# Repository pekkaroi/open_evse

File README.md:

# OpenEVSE

My fork has support for two contactors - one for 1 phase and one for 3 phase, and user can select the relay before starting charging. Change of the relay is forbidden during charging. To change the number of phases (to match with excess solar production), I have implemented a EspHome component connected to my OpenEvse directly with uart, and it first disables the charger (sleep), changes the relay to use, and then re-enables charge.

Additionally, as I accidentially ordered AtMega 328pb chips instead of 328p for my build, I had to modify the source accordinly.

Firmware for OpenEVSE controller used in OpenEVSE Charging Stations sold in the USA, and OpenEnergyMonitor EmonEVSE units sold in (UK/EU).

- OpenEVSE: <https://store.openevse.com/collections/all-products>
- EmonEVSE: <https://shop.openenergymonitor.com/evse/>

Based on OpenEVSE: Open Source Hardware J1772 Electric Vehicle Supply Equipment

## USA

TODO: add notes about USA OpenEVSE

## UK/EU

- Disable `AUTOSVCLEVEL` (autodetection is designed for split-phase)
- Charging level default to `L2`
- Set `MAX_CURRENT_CAPACITY_L2 32` (limit for single-phase charging in UK/EU)
- Add '.EU' to version number
- Enable LCD Redraw every couple of min (required for EMC/CE)

### EmonEVSE

EmonEVSE (non-tethered type-2 EVSE unit)

- `PP_AUTO_AMPACITY` enabled to set max current based on non-tethered cable connected
- Three-phase option with `THREEPHASE` enabled to calculate three-phase energy ( Unneeded with ESP32_WiFi firmware >= 4.2

## API Documentation

- WIFI API: <http://github.com/openevse/ESP32_WiFi_V4.x/>
- RAPI API: <https://github.com/openenergymonitor/open_evse/blob/master/firmware/open_evse/rapi_proc.h>

## Resources

- [OpenEnergyMonitor OpenEVSE Setup Guide](https://guide.openenergymonitor.org/integrations/openevse)
- [OpenEnergyMonitor OpenEVSE Shop](https://shop.openenergymonitor.com/ev-charging/)

- [OpenEVSE Controller Datasheet](https://github.com/OpenEVSE/OpenEVSE_PLUS/blob/master/OpenEVSE_PLUS_v5/OpenEVSE_Plus_v5.pdf)
- [OpenEVSE Controller Hardware Repo](https://github.com/OpenEVSE/OpenEVSE_PLUS)
- [OpenEVSE Project Homepage](https://openevse.com)

***

Firmware compile & upload help: [firmware/open_evse/LoadingFirmware.md](firmware/open_evse/LoadingFirmware.md)

NOTES:

- Working versions of the required libraries are included with the firmware code. This avoids potential issues related to using the wrong versions of the libraries.
- Highly recommend using the tested pre-compiled firmware (see releases page)

## Flash pre-compiled using avrdude

`$ avrdude -p atmega328p -B6 -c usbasp -P usb -e -U flash:w:firmware.hex`

ISP programmer required e.g [USBASP](https://www.amazon.co.uk/Hobby-Components-USBASP-Programmer-Adapter/dp/B06XYV162N)

### Set AVR fuses

This only needs to be done once in the factory

`avrdude -c USBasp -p m328p -U lfuse:w:0xFF:m -U hfuse:w:0xDF:m -U efuse:w:0xFD:m -B6`

If writing eFuse fails ISBasp may need a [firmware update](https://www.vishnumaiea.in/articles/electronics/how-to-solve-usbasp-avr-efuse-write-problem-on-progisp)

***

Tip Jar: I developed/maintain this firmware on a volunteer basis. Any donation, no matter how small, is greatly appreciated.

```text
Open EVSE is free software; you can redistribute it and/or modify
it under the terms of the GNU General Public License as published by
the Free Software Foundation; either version 3, or (at your option)
any later version.

Open EVSE is distributed in the hope that it will be useful,
but WITHOUT ANY WARRANTY; without even the implied warranty of
MERCHANTABILITY or FITNESS FOR A PARTICULAR PURPOSE.  See the
GNU General Public License for more details.

You should have received a copy of the GNU General Public License
along with Open EVSE; see the file COPYING.  If not, write to the
Free Software Foundation, Inc., 59 Temple Place - Suite 330,
Boston, MA 02111-1307, USA.

* Open EVSE is distributed in the hope that it will be useful,
* but WITHOUT ANY WARRANTY; without even the implied warranty of
* MERCHANTABILITY or FITNESS FOR A PARTICULAR PURPOSE.
```

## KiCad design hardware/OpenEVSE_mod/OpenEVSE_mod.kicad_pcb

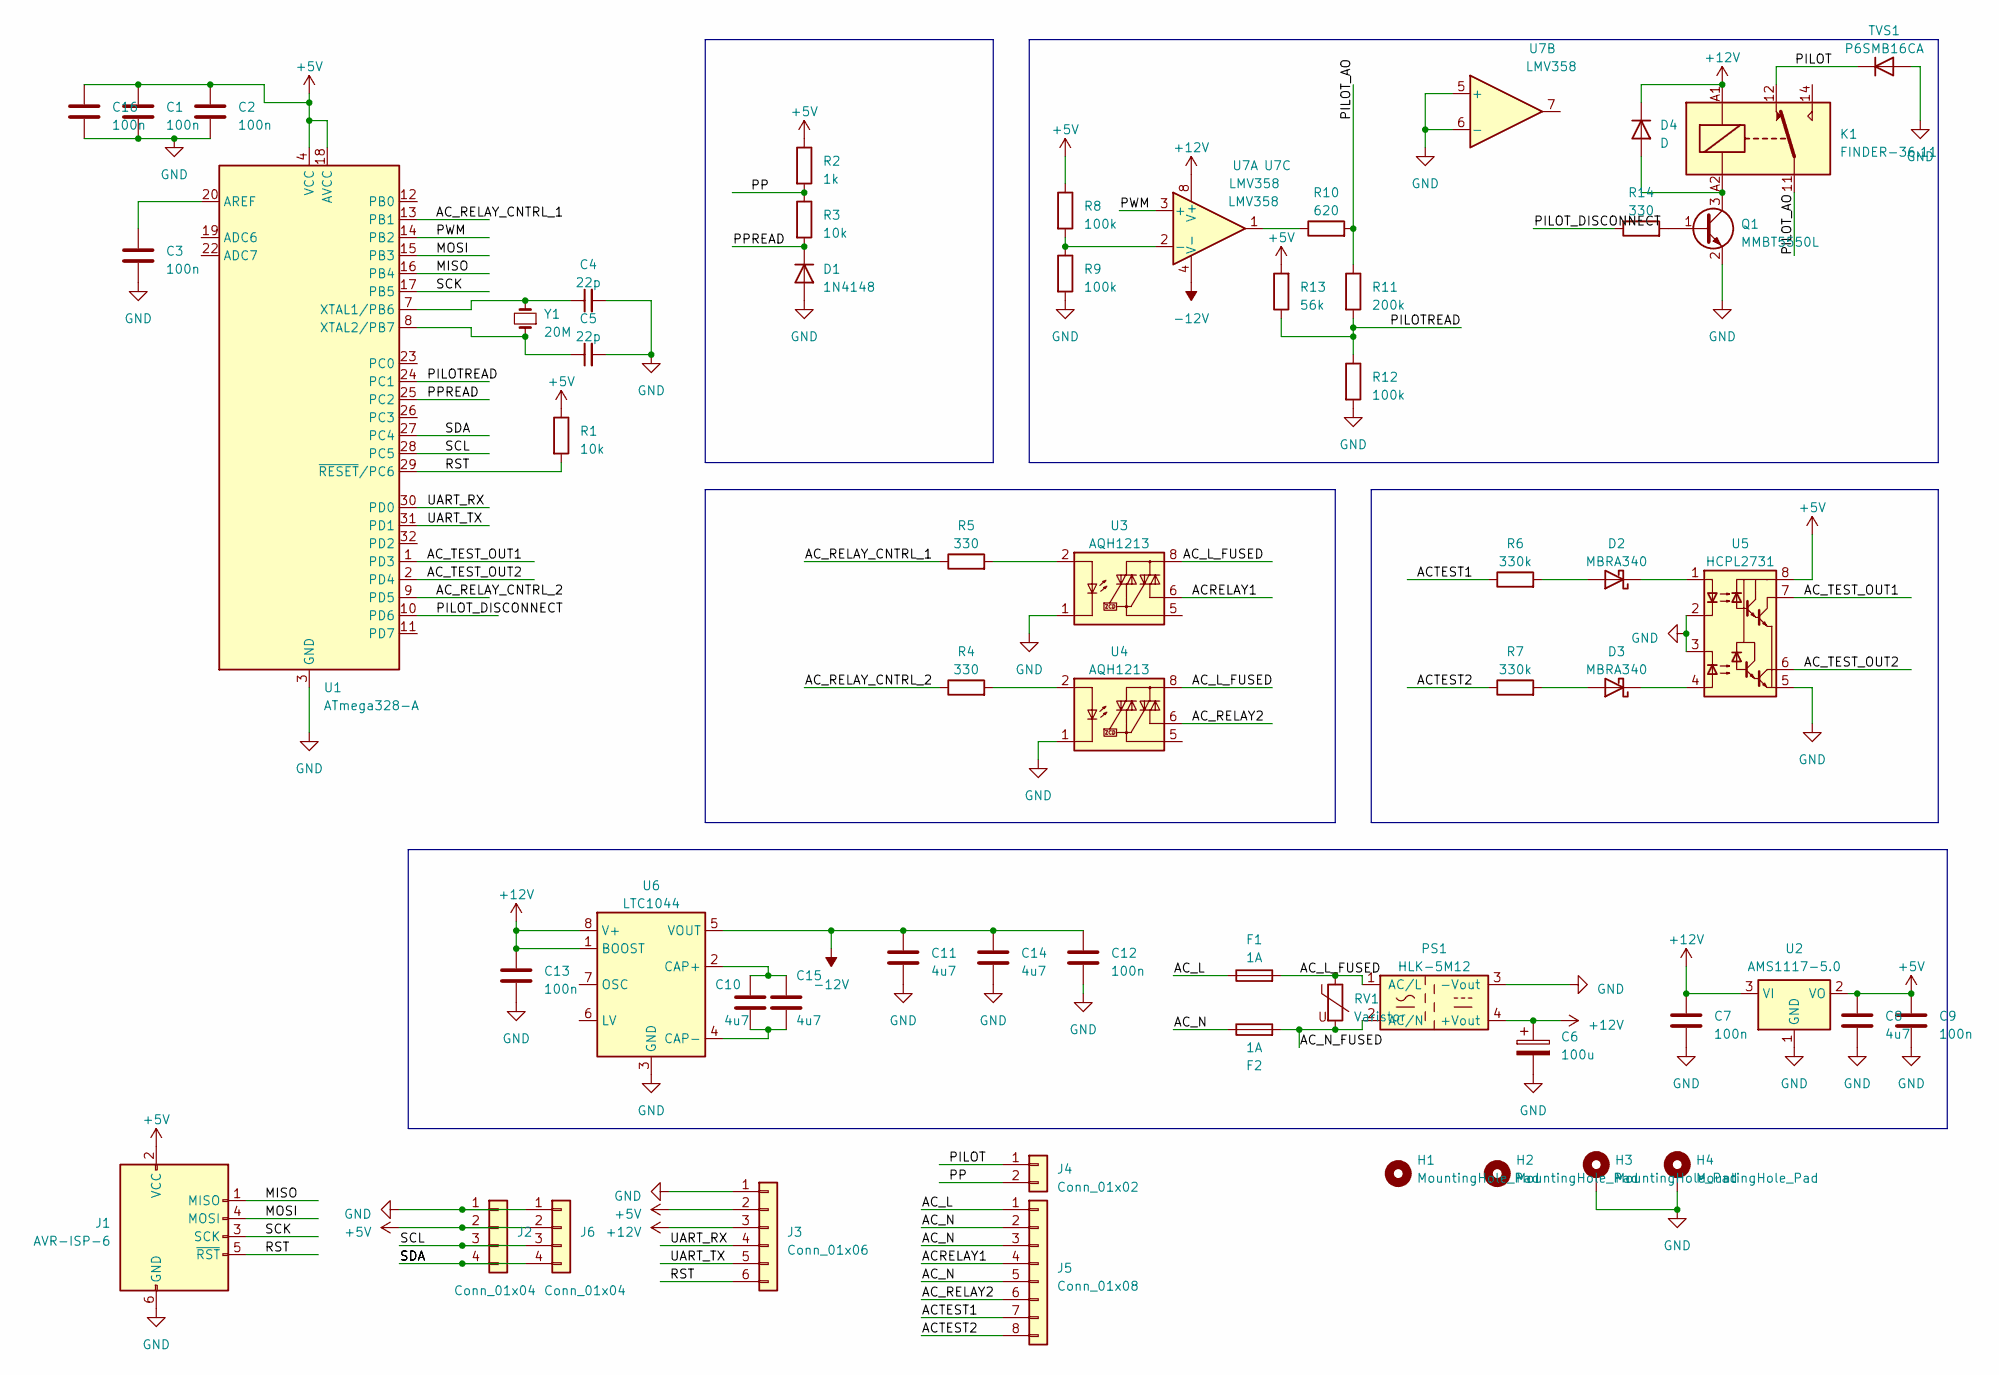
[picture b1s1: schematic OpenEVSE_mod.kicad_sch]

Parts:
C1, C2, C3, C7, C9, C12, C13, C16: 100n; C_0805_2012Metric_Pad1.18x1.45mm_HandSolder
C4, C5: 22p; C_0805_2012Metric_Pad1.18x1.45mm_HandSolder
C6: 100u; CP_Radial_D8.0mm_P3.50mm
C8, C10, C11, C14, C15: 4u7; C_0805_2012Metric_Pad1.18x1.45mm_HandSolder
D1: 1N4148; D_0402_1005Metric_Pad0.77x0.64mm_HandSolder
D2, D3: MBRA340; D_SMA
D4: D; D_SMB-SMC_Universal_Handsoldering
F1, F2: 1A; Fuse_Littelfuse_395Series
H1, H2: MountingHole_Pad; MountingHole_3.2mm_M3_ISO14580
H3, H4: MountingHole_Pad; MountingHole_3.2mm_M3_ISO14580_Pad_TopBottom
J1: AVR-ISP-6; PinHeader_2x03_P2.54mm_Vertical
J2, J6: Conn_01x04; PinSocket_1x04_P2.54mm_Vertical
J3: Conn_01x06; PinSocket_1x06_P2.54mm_Vertical
J4: Conn_01x02; TerminalBlock_Phoenix_PT-1,5-2-5.0-H_1x02_P5.00mm_Horizontal
J5: Conn_01x08; TerminalBlock_Phoenix_PT-1,5-8-5.0-H_1x08_P5.00mm_Horizontal
K1: FINDER-36.11; Relay_SPDT_Finder_36.11
PS1: HLK-5M12; Converter_ACDC_Hi-Link_HLK-5MXX_THT
Q1: MMBT5550L; SOT-23
R1, R3: 10k; R_0805_2012Metric_Pad1.20x1.40mm_HandSolder
R2: 1k; R_0805_2012Metric_Pad1.20x1.40mm_HandSolder
R4, R5, R14: 330; R_0805_2012Metric_Pad1.20x1.40mm_HandSolder
R6, R7: 330k; R_Axial_DIN0309_L9.0mm_D3.2mm_P15.24mm_Horizontal
R8, R9, R12: 100k; R_0805_2012Metric_Pad1.20x1.40mm_HandSolder
R10: 620; R_0805_2012Metric_Pad1.20x1.40mm_HandSolder
R11: 200k; R_0805_2012Metric_Pad1.20x1.40mm_HandSolder
R13: 56k; R_0805_2012Metric_Pad1.20x1.40mm_HandSolder
RV1: Varistor; RV_Disc_D12mm_W3.9mm_P7.5mm
TVS1: P6SMB16CA; D_SMB_Handsoldering
U1: ATmega328-A; TQFP-32_7x7mm_P0.8mm
U2: AMS1117-5.0; SOT-223-3_TabPin2
U3, U4: AQH1213; DIP-8-N7_W7.62mm
U5: HCPL2731; DIP-8_W7.62mm
U6: LTC1044; SOIC-8_3.9x4.9mm_P1.27mm
U7: LMV358; SOIC-8_3.9x4.9mm_P1.27mm
Y1: 20M; Crystal_HC49-U_Vertical

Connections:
+5V: C1.1, C2.1, C8.1, C9.1, C16.1, J1.2 (VCC), J2.2, J3.2, J6.2, R1.1, R2.1, R8.1, R13.2, U1.4 (VCC), U1.6 (VCC), U1.18 (AVCC), U2.2 (VO), U5.8 (VCC)
+12V: C6.1, C7.1, C13.1, D4.1 (K), J3.3, K1.A1, PS1.4 (+Vout), U2.3 (VI), U6.1 (BOOST), U6.8 (V+), U7.8 (V+)
-12V: C11.1, C12.1, C14.1, U6.5 (VOUT), U7.4 (V-)
/ACRELAY1: J5.4, U3.6
/ACTEST1: J5.7, R6.1
/ACTEST2: J5.8, R7.1
/AC_L: F1.1, J5.1
/AC_L_FUSED: F1.2, PS1.1 (AC/L), RV1.1, U3.8, U4.8
/AC_N: F2.1, J5.2, J5.3, J5.5
/AC_N_FUSED: F2.2, PS1.2 (AC/N), RV1.2
/AC_RELAY2: J5.6, U4.6
/AC_RELAY_CNTRL_1: R5.1, U1.13 (PB1)
/AC_RELAY_CNTRL_2: R4.1, U1.9 (PD5)
/AC_TEST_OUT1: U1.1 (PD3), U5.7 (VO1)
/AC_TEST_OUT2: U1.2 (PD4), U5.6 (VO2)
/MISO: J1.1 (MISO), U1.16 (PB4)
/MOSI: J1.4 (MOSI), U1.15 (PB3)
/PILOT: J4.1, K1.12, TVS1.1 (K)
/PILOTREAD: R11.2, R12.1, R13.1, U1.24 (PC1)
/PILOT_AO: K1.11, R10.2, R11.1
/PILOT_DISCONNECT: R14.1, U1.10 (PD6)
/PP: J4.2, R2.2, R3.1
/PPREAD: D1.1 (K), R3.2, U1.25 (PC2)
/PWM: U1.14 (PB2), U7.3 (+)
/RST: J1.5 (~RST), J3.6, R1.2, U1.29 (~RESET/PC6)
/SCK: J1.3 (SCK), U1.17 (PB5)
/SCL: J2.3, J6.3, U1.28 (PC5)
/SDA: J2.4, J6.4, U1.27 (PC4)
/UART_RX: J3.4, U1.30 (PD0)
/UART_TX: J3.5, U1.31 (PD1)
GND: C1.2, C2.2, C3.2, C4.2, C5.2, C6.2, C7.2, C8.2, C9.2, C11.2, C12.2, C13.2, C14.2, C16.2, D1.2 (A), H3.1, H4.1, J1.6 (GND), J2.1, J3.1, J6.1, PS1.3 (-Vout), Q1.2 (E), R9.2, R12.2, TVS1.2 (A), U1.3 (GND), U1.5 (GND), U1.21 (GND), U2.1 (GND), U3.1, U3.3, U3.4, U4.1, U4.3, U4.4, U5.2 (C1), U5.3 (C2), U5.5 (GND), U6.3 (GND), U7.5 (+), U7.6 (-)
unnamed: D2.2 (A), R6.2
unnamed: D2.1 (K), U5.1 (A1)
unnamed: D3.2 (A), R7.2
unnamed: D3.1 (K), U5.4 (A2)
unnamed: D4.2 (A), K1.A2, Q1.3 (C)
unnamed: Q1.1 (B), R14.2
unnamed: R4.2, U4.2
unnamed: R5.2, U3.2
unnamed: R10.1, U7.1
unnamed: C3.1, U1.20 (AREF)
unnamed: C4.1, U1.7 (XTAL1/PB6), Y1.2
unnamed: C5.1, U1.8 (XTAL2/PB7), Y1.1
unnamed: C10.1, C15.1, U6.2 (CAP+)
unnamed: C10.2, C15.2, U6.4 (CAP-)
unnamed: R8.2, R9.1, U7.2 (-)

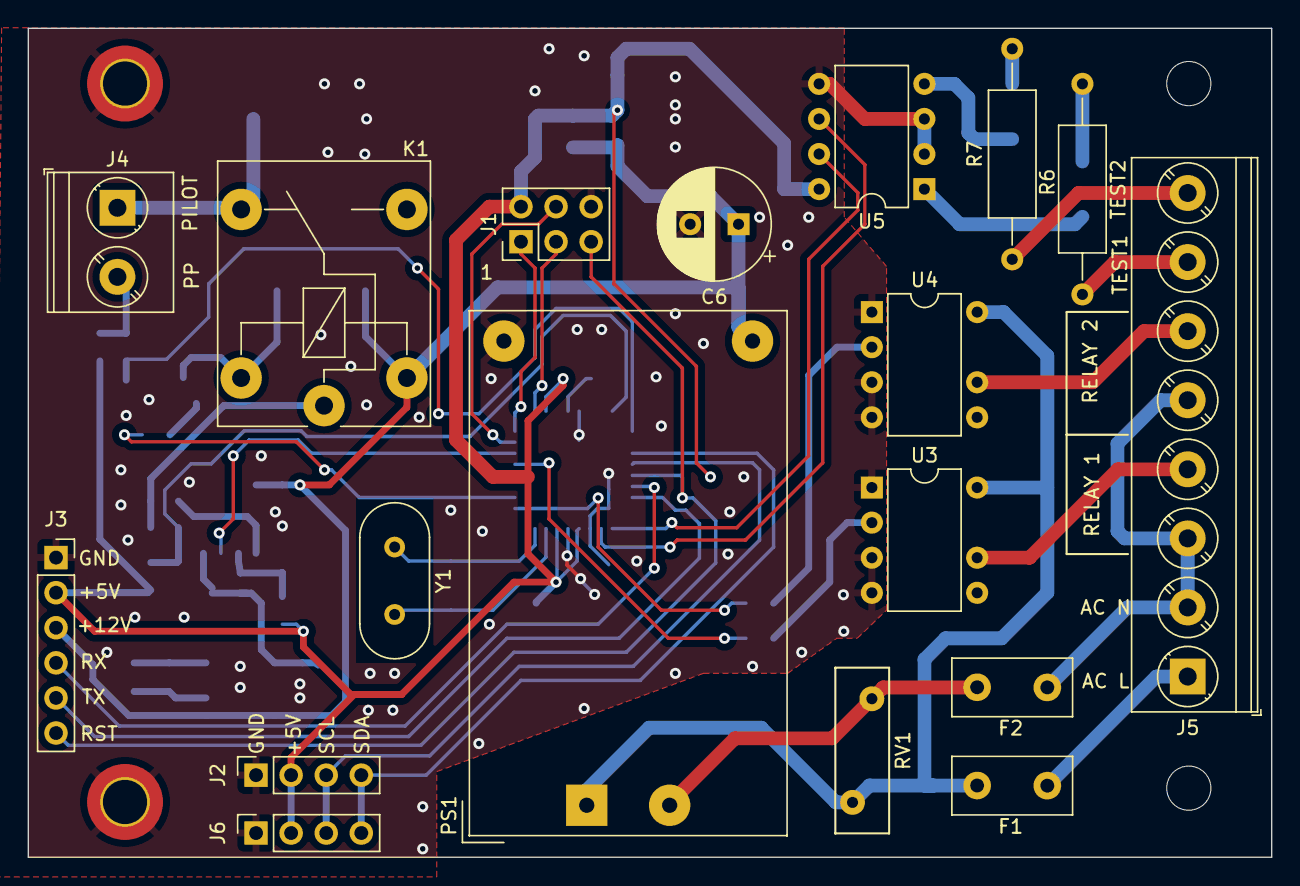
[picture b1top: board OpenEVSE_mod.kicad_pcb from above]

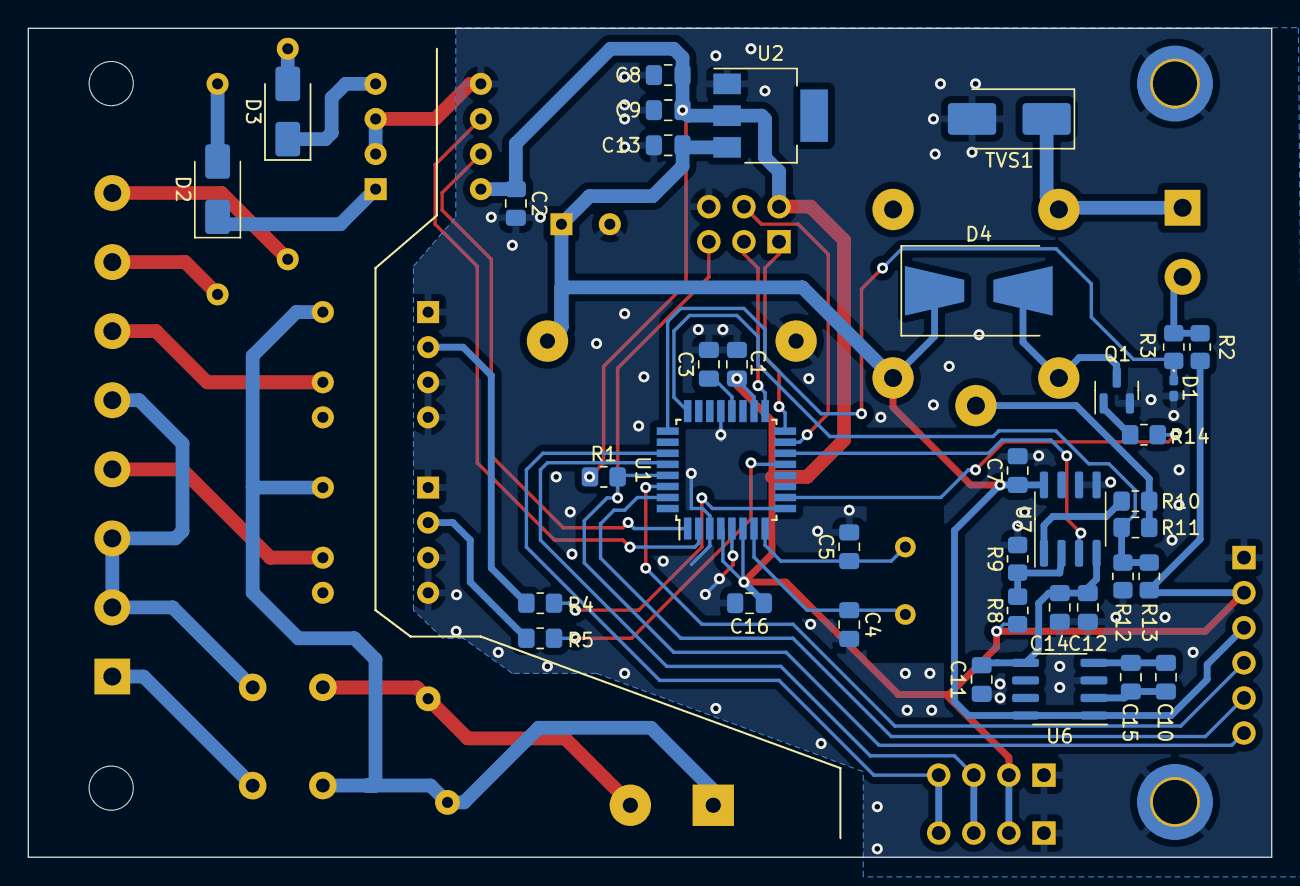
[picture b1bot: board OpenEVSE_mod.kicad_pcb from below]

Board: 2 copper layers, 90.0 x 60.0 mm, 59 parts (38 on the bottom side), 46 nets.

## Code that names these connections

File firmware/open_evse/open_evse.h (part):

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// when closing DC relay set to HIGH for m_relayCloseMs, then
// switch to m_relayHoldPwm
// ONLY WORKS PWM-CAPABLE PINS!!!
// use Arduino pin number PD5 = 5, PD6 = 6
//#define RELAY_PWM
#define DEFAULT_RELAY_CLOSE_MS 100
#define DEFAULT_RELAY_HOLD_PWM 255 // (0-255, where 0=0%, 255=100%
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//J1772EVSEController

#define CURRENT_PIN 0 // analog current reading pin ADCx
#define PILOT_PIN 1 // analog pilot voltage reading pin ADCx
#define PP_PIN 2 // PP_READ - ADC2
#ifdef VOLTMETER
// N.B. Note, ADC2 is already used as PP_PIN so beware of potential clashes
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//#define GREEN_LED_IDX 5
#endif // OPENEVSE_2

// N.B. if PAFC_PWM is enabled, then pilot pin can be PB1 or PB2
// if using fast PWM (PAFC_PWM disabled) pilot pin *MUST* be PB2
#define PILOT_REG &PINB
#define PILOT_IDX 2

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#define V6_ID_IDX 7

#ifdef GFI
#define GFI_INTERRUPT 0 // interrupt number 0 = PD2, 1 = PD3
// interrupt number 0 = PD2, 1 = PD3
#define GFI_REG &PIND
#define GFI_IDX 2

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
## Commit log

2023-02-04 Merge OpenEVES/OpenEnergyMonitor changes to the new `master` branch (#14)
    Creating a new master branch fron Lincomatic's master branch with a squash merge of the stable changes from OpenEVSE/OpenEnergyMonitor. This will make it easier to track and merge changes from the up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
    ---
    * don't enable MENNEKES_LOCK since hardware wont be availabe initally
    * fix merge typo
    * set upload device
    * set BOD fuse
2023-02-04 Updated to use new `master`
2023-04-11 remove emonevse_3ph from github action build
2023-04-15 put back RAPI_WF
2023-04-24 Fix missing temperature sensor ( i2c was reset after temp sensor initialisation )
2023-04-24 set default voltage to 230V for EU builds
2023-04-28 Removing some old envs that are no longer supported
2023-05-03 L2 default for EU
2023-05-29 Update LoadingFirmware.md
    Fixed typo
2025-01-06 Update platformio.ini
    Add support for Continuous Ground Monitoring on OpenEVSE v6+ hardware
2025-01-07 Update platformio.ini
    Remove Bootlock for, US builds
2025-03-20 Added support for 1/3 phases. Changed microcontroller to m328b
2025-03-20 added pcb
